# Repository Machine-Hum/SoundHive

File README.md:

SoundHive
=========

SoundHive is a 1" x 1" open source audio amplifier, designed to be stacked much like Arduino, the
aim is to reduce electronic waste by utilizing existing speakers without having to buy new amplifier
equipment. It also increased modularity and customization, much of the design in still in the initial phase.

Amp - 1W
--------
Working, tested simple 1W audio amp based on LM386.

Amp - 15W
--------
In progress, 15W amp based on MP774 class D amp.

AuxBreak
--------
Breaks out standard 3.5mm audio jack.

PowerBreak
--------
Breaks out standard 2.1mm barrel connectors - for powering the whole stack.

/IMG_5097.JPG)

/IMG_5098.JPG)

-Walker (Machinehum)

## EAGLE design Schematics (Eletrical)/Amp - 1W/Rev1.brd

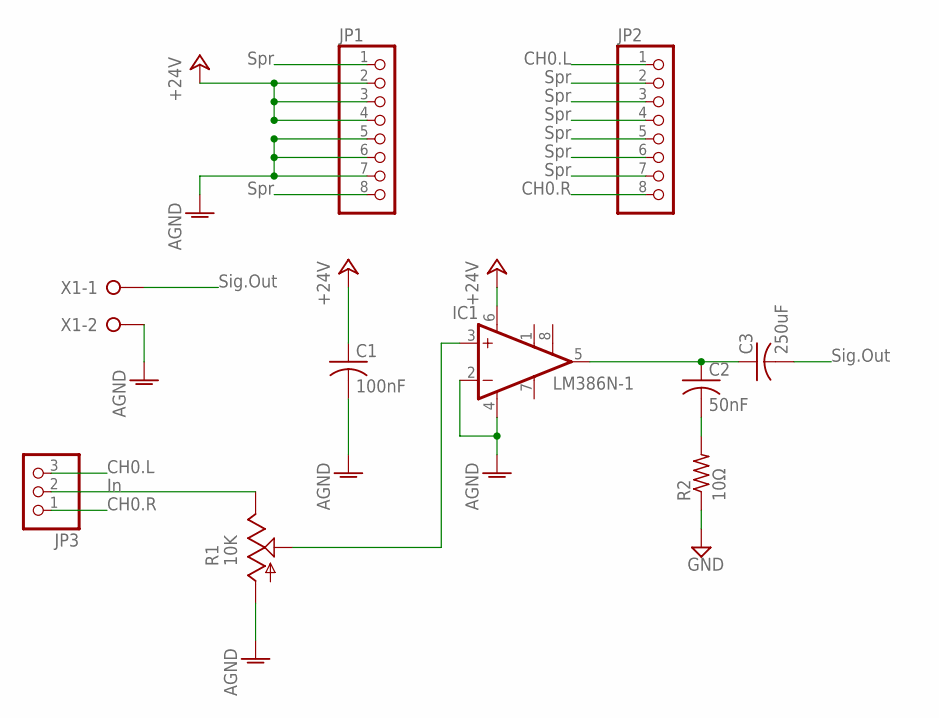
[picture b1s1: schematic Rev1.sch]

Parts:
C1: 100nF; C075-032X103
C2: 50nF; C075-032X103
C3: 250uF; C025-050X050
IC1: LM386N-1; DIL08
JP1, JP2: PINHD-1X8; 1X08
JP3: PINHD-1X3; 1X03
R1: 10K; PT-10S
R2: 10Ω; 0204/7
X1: W237-02P; W237-132

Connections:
+24V: C1.1, IC1.6 (VS), JP1.2, JP1.3, JP1.4
AGND: C1.2, IC1.2 (-IN), IC1.4 (GND), JP1.5, JP1.6, JP1.7, R1.A, X1.2
CH0.L: JP2.1, JP3.3
CH0.R: JP2.8, JP3.1
GND: R2.1
JP1-P1: JP1.1
JP1-P2: JP1.8
JP2-P2: JP2.2
JP2-P3: JP2.3
JP2-P4: JP2.4
JP2-P5: JP2.5
JP2-P6: JP2.6
JP2-P7: JP2.7
unnamed: C2.1, C3.1, IC1.5 (OUT)
unnamed: IC1.3 (+IN), R1.S
unnamed: JP3.2, R1.E
unnamed: C2.2, R2.2
SIGOUT: C3.2, X1.1

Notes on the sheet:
Spr
CH0.L
CH0.R
Sig.Out

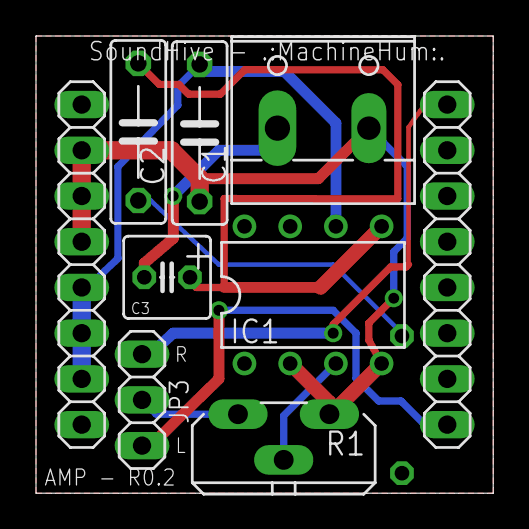
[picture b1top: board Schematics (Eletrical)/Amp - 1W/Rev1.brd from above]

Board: 2 copper layers, 25.4 x 25.4 mm, 10 parts (1 on the bottom side), 9 nets.

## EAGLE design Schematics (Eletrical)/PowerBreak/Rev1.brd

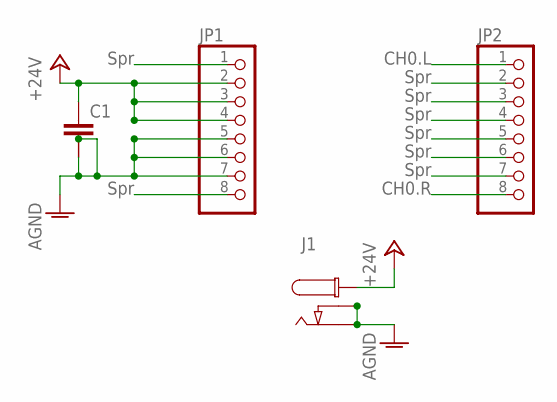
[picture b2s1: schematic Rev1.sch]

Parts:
C1: C-2.5-5/6; C2.5/5-6
J1: CON_DC_M-DC_PTH; DC_BARREL_JACK_PTH_2MM
JP1, JP2: PINHD-1X8; 1X08

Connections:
+24V: C1.1, J1.P1, JP1.2, JP1.3, JP1.4
AGND: C1.2, C1.3, J1.P2 (P3), J1.P3 (P2), JP1.5, JP1.6, JP1.7
CH0.L: JP2.1
CH0.R: JP2.8
JP1-P1: JP1.1
JP1-P2: JP1.8
JP2-P2: JP2.2
JP2-P3: JP2.3
JP2-P4: JP2.4
JP2-P5: JP2.5
JP2-P6: JP2.6
JP2-P7: JP2.7

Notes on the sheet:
Spr
CH0.L
CH0.R

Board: 2 copper layers, 4 parts (0 on the bottom side), 2 nets, no tracks yet.

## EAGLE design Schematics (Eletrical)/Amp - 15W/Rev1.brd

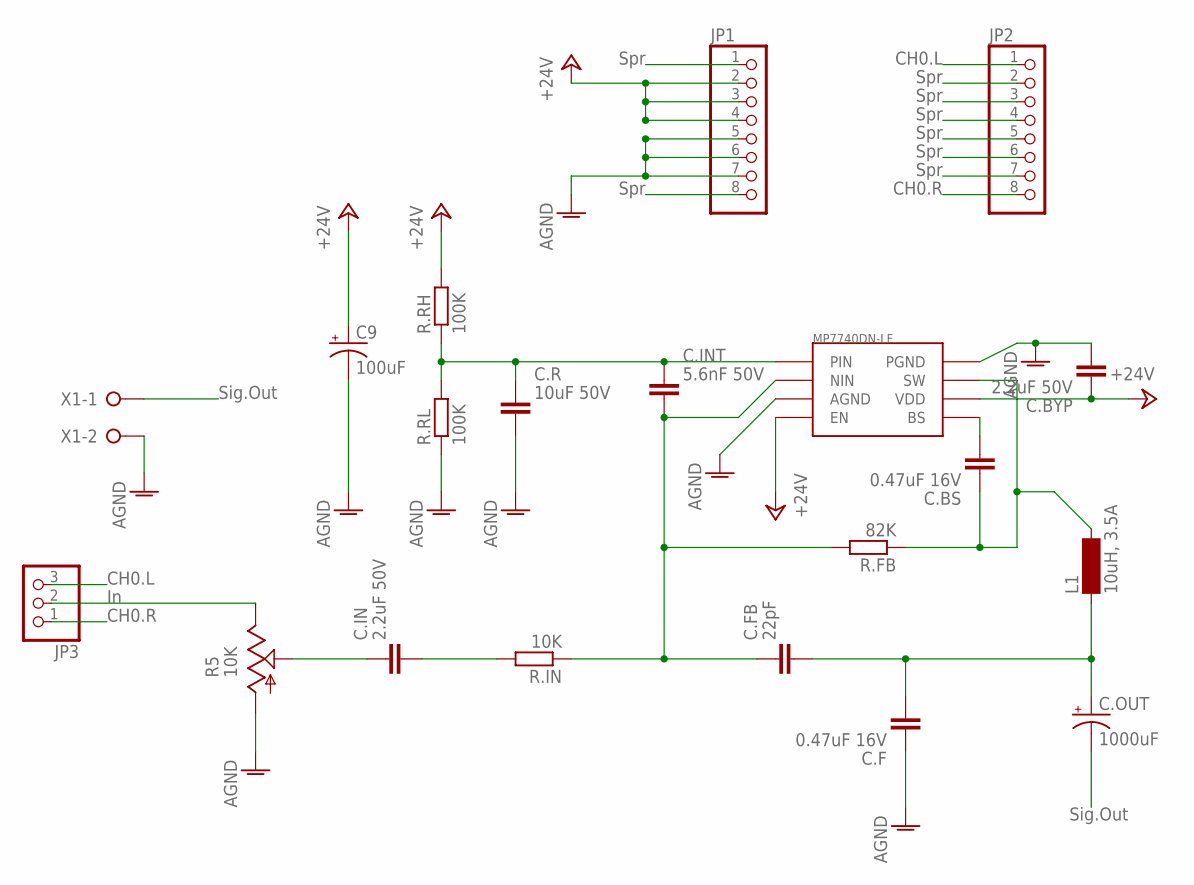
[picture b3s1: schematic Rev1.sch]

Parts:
C9: 100uF; E5-4
C.BS, C.F: 0.47uF 16V; C805
C.BYP, C.IN: 2.2uF 50V; C805
C.FB: 22pF; C603
C.INT: 5.6nF 50V; C603
C.OUT: 1000uF; E5-4
C.R: 10uF 50V; C1206
JP1, JP2: PINHD-1X8; 1X08
JP3: PINHD-1X3; 1X03
L1: 10uH, 3.5A; BS11
R5: 10K; PT-10S
R.FB: 82K; R805
R.IN: 10K; R805
R.RH, R.RL: 100K; R603
U$1: MP7740DN-LF; SOIC8
X1: W237-02P; W237-132

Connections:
+24V: C9.+, C.BYP.1, JP1.2, JP1.3, JP1.4, R.RH.2, U$1.4 (EN), U$1.6 (VDD)
AGND: C9.-, C.BYP.2, C.F.1, C.R.2, JP1.5, JP1.6, JP1.7, R5.A, R.RL.1, U$1.3 (AGND), U$1.8 (PGND), X1.2
CH0.L: JP2.1, JP3.3
CH0.R: JP2.8, JP3.1
JP1-P1: JP1.1
JP1-P2: JP1.8
JP2-P2: JP2.2
JP2-P3: JP2.3
JP2-P4: JP2.4
JP2-P5: JP2.5
JP2-P6: JP2.6
JP2-P7: JP2.7
unnamed: C.INT.1, C.R.1, R.RH.1, R.RL.2, U$1.1 (PIN)
unnamed: C.FB.1, C.INT.2, R.FB.2, R.IN.1, U$1.2 (NIN)
unnamed: C.IN.2, R.IN.2
unnamed: C.BS.2, U$1.5 (BS)
unnamed: C.BS.1, L1.2, R.FB.1, U$1.7 (SW)
unnamed: JP3.2, R5.E
unnamed: C.IN.1, R5.S
unnamed: C.F.2, C.FB.2, C.OUT.+, L1.1
SIGOUT: C.OUT.-, X1.1

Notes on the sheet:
Spr
CH0.L
CH0.R
Sig.Out

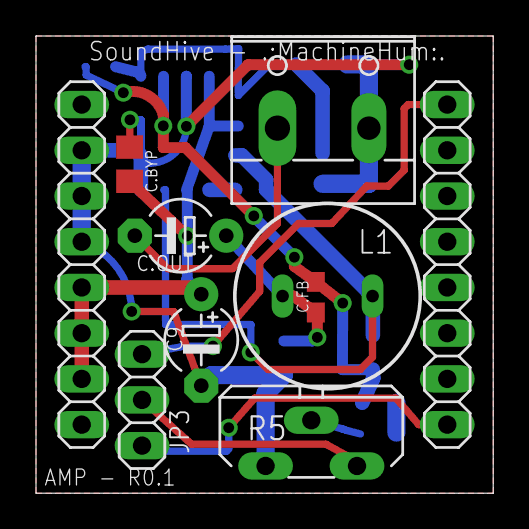
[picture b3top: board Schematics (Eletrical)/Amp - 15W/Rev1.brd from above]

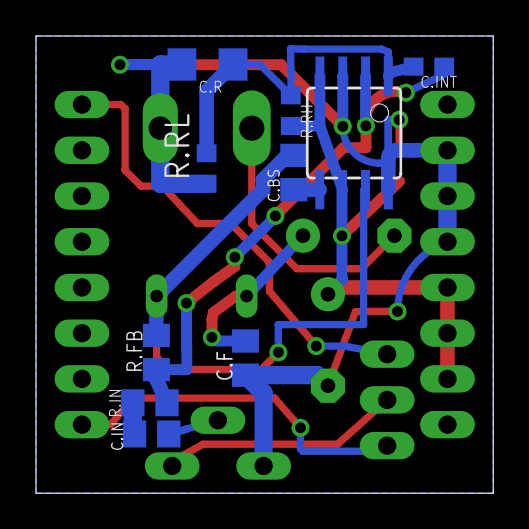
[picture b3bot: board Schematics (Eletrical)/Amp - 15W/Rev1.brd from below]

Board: 2 copper layers, 25.4 x 25.4 mm, 20 parts (10 on the bottom side), 13 nets.

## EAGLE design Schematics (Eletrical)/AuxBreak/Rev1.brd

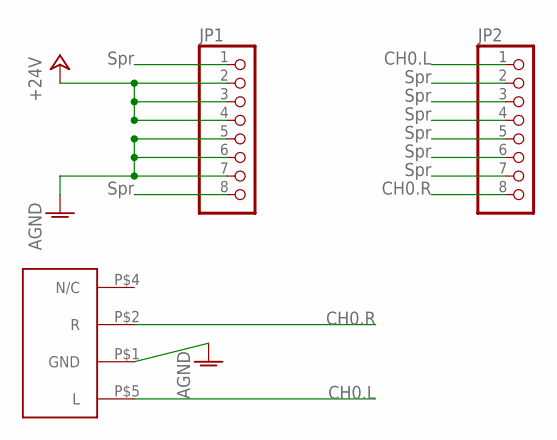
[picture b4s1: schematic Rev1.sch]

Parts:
JP1, JP2: PINHD-1X8; 1X08
U$1: 161-3509-E

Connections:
+24V: JP1.2, JP1.3, JP1.4
AGND: JP1.5, JP1.6, JP1.7, U$1.P$1 (GND)
CH0.L: JP2.1, U$1.P$5 (L)
CH0.R: JP2.8, U$1.P$2 (R)
JP1-P1: JP1.1
JP1-P2: JP1.8
JP2-P2: JP2.2
JP2-P3: JP2.3
JP2-P4: JP2.4
JP2-P5: JP2.5
JP2-P6: JP2.6
JP2-P7: JP2.7

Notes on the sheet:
Spr
CH0.L
CH0.R

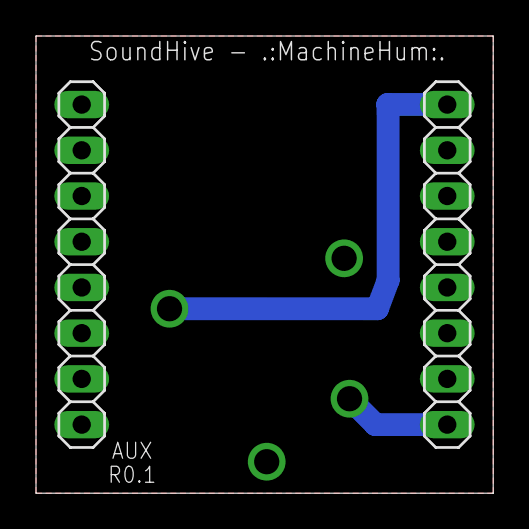
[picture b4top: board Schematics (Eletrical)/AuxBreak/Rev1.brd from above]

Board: 2 copper layers, 25.4 x 25.4 mm, 3 parts (1 on the bottom side), 4 nets.

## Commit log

2016-01-25 new file: Schematics (Eletrical)/Amp - 15W/Rev1.b#1 new file: Schematics (Eletrical)/Amp - 15W/Rev1.b#2 new file: Schematics (Eletrical)/Amp - 15W/Rev1.b#3 new file: Schematics (Eletrical)/Amp - 15W/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
2016-01-25 deleted: Schematics (Eletrical)/Amp - 15W/Rev1.b#1 deleted: Schematics (Eletrical)/Amp - 15W/Rev1.b#2 deleted: Schematics (Eletrical)/Amp - 15W/Rev1.b#3 deleted: Schematics (Eletrical)/Amp - 15W/Rev1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
2016-01-25 new file: Media (Pictures & Videos)/IMG_5097.JPG new file: Media (Pictures & Videos)/IMG_5098.JPG new file: README.txt
2016-03-07 Rename README.txt to README.md
2016-03-07 Rename README.md to README.rst
2016-03-07 Rename README.rst to README.md
